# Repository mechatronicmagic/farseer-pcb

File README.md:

- [Repository Info](#org3efd3b6)
- [Images](#org4000d6c)
- [Schematic](#org9702aa9)
- [PCB](#orgc4c3abc)
- [Bill of Materials](#org9a89b54)
- [Development](#org04cc7a2)

    <!-- This file is generated automatically from metadata -->
    <!-- File edits may be overwritten! -->

# Repository Info

-   Project Name: farseer\_pcb
-   Synopsis: Measures fly wingbeats using IR light reflected from flapping fly wings.
-   Documentation Version: 1.0.0
-   Pcb Version: 1.0
-   Enclosure Version: 1.0
-   Supplemental BOM Version: 1.0
-   Release Date: 2025-05-16
-   Creation Date: 2025-05-16
-   Kicad Version: 9.0.0
-   License: GPL-3.0
-   URL: <https://github.com/mechatronicmagic/farseer_pcb>
-   Author: Peter Polidoro
-   Email: peter@polidoro.io
-   Copyright: 2025 Peter Polidoro
-   References:
    -   [kicad](https://www.kicad.org/)
    -   [light\_sensor\_boards](https://github.com/janelia-kicad/light_sensor_boards)
    -   [wingbeat\_detector](https://github.com/peterpolidoro/wingbeat_detector)
-   Papers:
    -   [Active antennal movements in Drosophila can tune wind encoding](https://doi.org/10.1016/j.cub.2023.01.020)
    -   [A novel assay to evaluate action selection in escape behavior](https://doi.org/10.1016/j.jneumeth.2018.04.019)
    -   [Cellular evidence for efference copy in Drosophila visuomotor processing](https://doi.org/10.1038/nn.4083)
    -   [State-dependent decoupling of sensory and motor circuits underlies behavioral flexibility in Drosophila](https://doi.org/10.1038/s41593-019-0413-4)
    -   [Active flight increases the gain of visual motion processing in Drosophila](https://doi.org/10.1038/nn.2492)
    -   [An Optical Tachometer for Measurement of the Wing-Beat Frequency of Free-Flying Insects](https://doi.org/10.1242/jeb.82.1.377)

This wingbeat detector, or flight “tachometer”, is a small electro-optical device that uses reflected infrared light from the fly’s wingbeats to generate an oscillating voltage signal. The oscillation frequency of the voltage signal matches, and thus allows one to measure, the tethered fly's wingbeat frequency.

This device is useful for plate (rather than pin) tethered flight experiments, because with plate-glued flies, one cannot extract the wingbeat frequency via a classical wingbeat analyzer. Microphones have also been used for extracting wingbeat frequency, but they require a quiet room. This wingbeat detector is immune to audible noise and only requires an infrared light source, often already present on flight rigs for video recording.

One end of a small diameter light guide is mounted near the fly and aimed at the wings. The other end of the light guide is in a small enclosure containing an optical filter and printed circuit board and can be mounted off to the side of the rig wherever there is room.

The light guide brings light reflected off of the wings down to a photodiode on a circuit board, after passing through an optical filter to remove the unwanted wavelengths of light. Amplifiers and filters on the circuit board convert the tiny amounts of current from the photodiode into an oscillating voltage signal, with a frequency range of several hundred Hertz and a magnitude range of several Volts.

The oscillating voltage signal can be fed into a data acquisition card, oscilloscope, and/or a speaker for recording and instant feedback on fly wingbeat frequency. Using a threshold, the signal can be used as a simple boolean that indicates whether the tethered animal is flying or not for triggering experiments or synchronizing the data collection.

This device was first created at Caltech in the Dickinson lab in collaboration with Gaby Maimon around 2010. It has transformed over several generations, getting smaller and more robust each iteration. It has been used on rigs in multiple universities and research institutes and has been referenced in several papers. A couple of iterations were designed in collaboration with Sung Soo Kim and the Card lab at Janelia Research Campus. The latest version was created in collaboration with the Suver lab at Vanderbilt.

# Images

# Schematic

[./documentation/schematic/wingbeat\_detector.pdf](./documentation/schematic/wingbeat_detector.pdf)

# PCB

# Bill of Materials

## Board

|    |
|--- |
|  |

## Supplemental

| Item | Description                        | Manufacturer Part Number | Manufacturer        | Quantity | Cost   | Total   |
|---- |---------------------------------- |------------------------ |------------------- |-------- |------ |------- |
| 1    | BNC STRAIGHT BULKHEAD JACK TO AM   | 095-850-210-150          | Amphenol RF         | 1        | 24.41  | 24.41   |
| 2    | AC/DC WALL MNT ADAPTER 5.1V 15W    | SC0445                   | Raspberry Pi        | 1        | 8.00   | 8.00    |
| 3    | CBL ASSY BNC PLUG-PLUG RG58 5'     | 5697-60                  | Pomona Electronics  | 1        | 21.29  | 21.29   |
| 4    | LLG 3 mm Core 420 - 2000 nm 1.2 m  | LLG3-4Z                  | thorlabs            | 1        | 392.69 | 392.69  |
| 5    | 3 mm LLG to SM1 Adapter            | AD3LLG                   | thorlabs            | 1        | 38.32  | 38.32   |
| 6    | Adapter External SM05 Internal SM1 | SM1A1                    | thorlabs            | 1        | 23.41  | 23.41   |
| 7    | SM05 Adjustable Lens Tube          | SM05V05                  | thorlabs            | 1        | 31.64  | 31.64   |
| 8    | 825nm 12.5mm Dia Longpass Filter   | 86-062                   | edmundoptics        | 1        | 194.00 | 194.00  |
| 9    | Universal probe holder             | MXB                      | siskiyou            | 1        | 275.00 | 275.00  |
| 10   | MACHINE SCREW PAN PHILLIPS 2-56    | PMSSS 256 0050 PH        | B&F Fastener Supply | 4        | 0.24   | 0.96    |
| 11   | HEX NUT 3/16" STN STEEL 2-56       | HNSS256                  | B&F Fastener Supply | 4        | 0.28   | 1.12    |
|      | Supplemental BOM Version: 1.0      |                          |                     |          | Total  | 1010.84 |

# Development

## Install Guix

[Install Guix](https://guix.gnu.org/manual/en/html_node/Binary-Installation.html)

## Edit metadata.org

    make metadata-edits

## Tangle metadata.org

    make metadata

## Edit project

    make kicad-edits
    exit

    make filter-edits
    exit

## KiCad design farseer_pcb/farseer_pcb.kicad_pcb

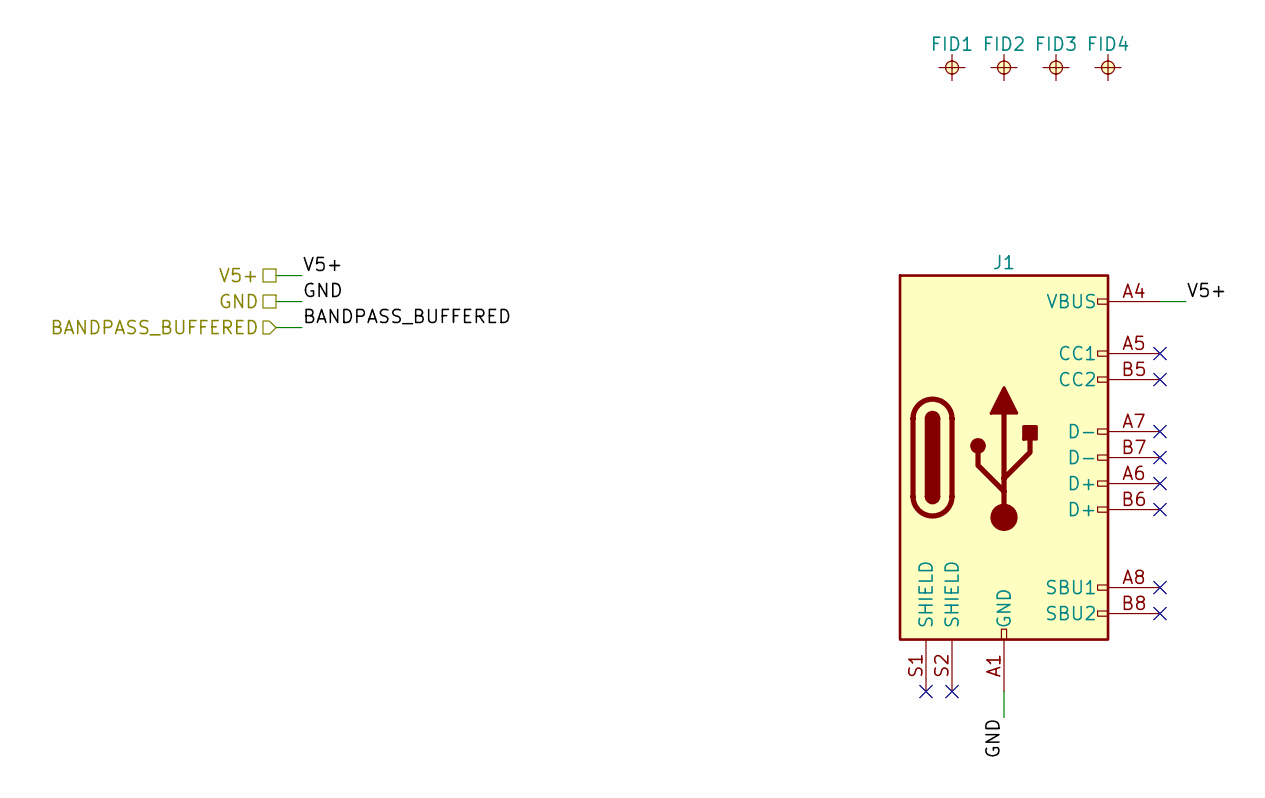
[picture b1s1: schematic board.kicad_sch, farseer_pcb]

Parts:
FID1, FID2, FID3, FID4: FIDUCIAL_0.5mm_MASK1mm; FIDUCIAL_0.5mm_Mask1mm
J1: Connector_USB_C_Receptacle_USB2.0_16P_GT-USB-7047C; USB_C_Receptacle_GT-USB-7047C_16P_TopMnt_Horizontal; Manufacturer Part Number GT-USB-7047C; LCSC C963218

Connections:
/GND: J1.A1 (GND), J1.A12 (GND), J1.B1 (GND), J1.B12 (GND); also elsewhere on the board
/V5+: J1.A4 (VBUS), J1.A9 (VBUS), J1.B4 (VBUS), J1.B9 (VBUS); also elsewhere on the board

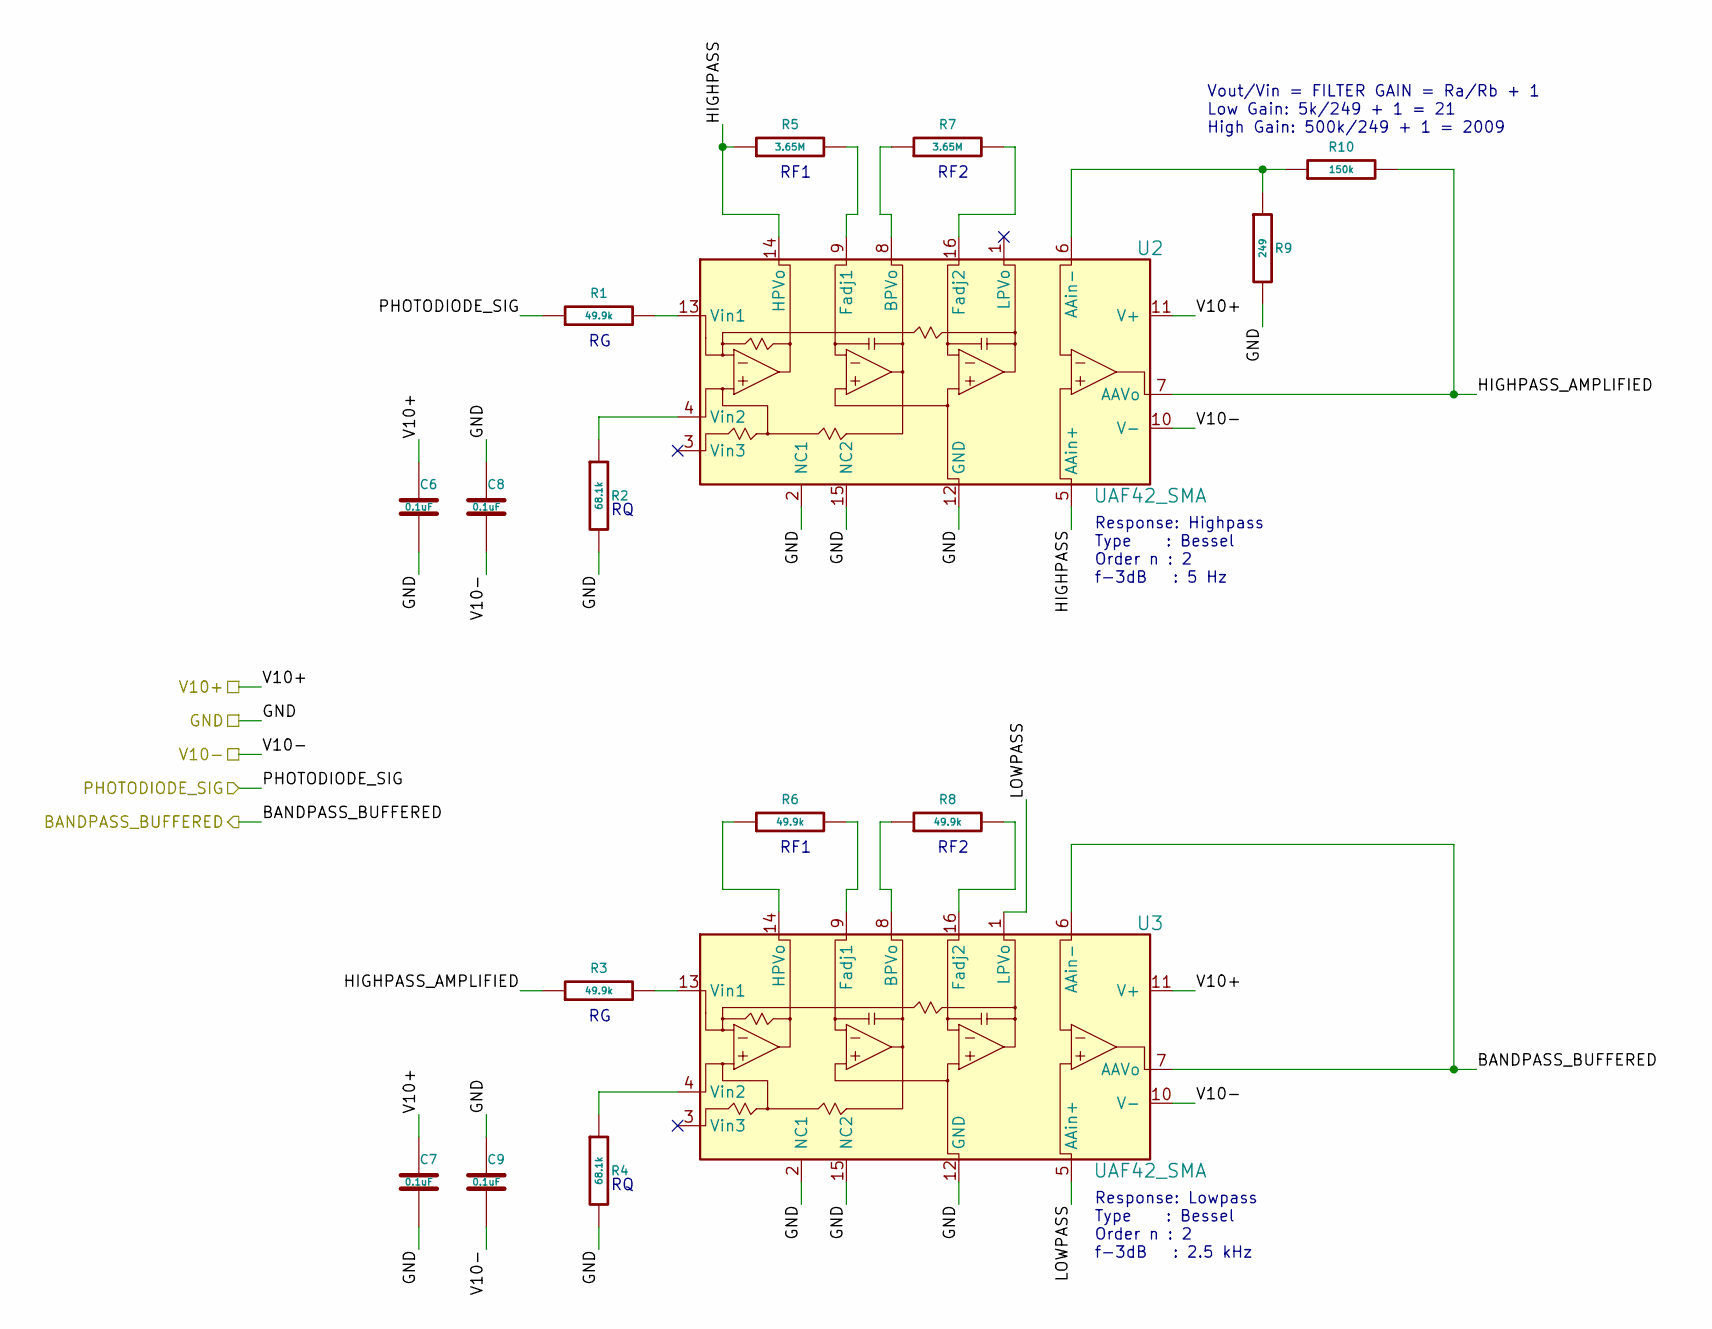
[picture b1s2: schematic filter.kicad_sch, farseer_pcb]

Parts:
C6, C7, C8, C9: 0.1uF; C_0402_1005Metric; Manufacturer Part Number CC0402ZRY5V8BB104
R1, R3, R6, R8: 49.9k; R_0402_1005Metric; Manufacturer Part Number ERJ-2RKF4992X
R2, R4: 68.1k; R_0402_1005Metric; Manufacturer Part Number ERJ-2RKF6812X
R5, R7: 3.65M; R_0603_1608Metric; Manufacturer Part Number CRCW06033M65FKEA
R9: 249; R_0402_1005Metric; Manufacturer Part Number ERJ-2RKF2490X
R10: 150k; R_1206_3216Metric; Manufacturer Part Number ERA-8AEB154V
U2, U3: UAF42_SMA; SOIC-16W_7.5x10.3mm_P1.27mm; Manufacturer Part Number UAF42AU

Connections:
/BANDPASS_BUFFERED: U3.6 (AAin-), U3.7 (AAVo)
/GND: C6.2, C7.2, C8.1, C9.1, R2.2, R4.2, R9.2, U2.2 (NC1), U2.12 (GND), U2.15 (NC2), U3.2 (NC1), U3.12 (GND), U3.15 (NC2); also elsewhere on the board
/PHOTODIODE_SIG: R1.1; also elsewhere on the board
/V10+: C6.1, C7.1, U2.11 (V+), U3.11 (V+); also elsewhere on the board
/V10-: C8.2, C9.2, U2.10 (V-), U3.10 (V-); also elsewhere on the board
/filter/HIGHPASS: R5.1, U2.5 (AAin+), U2.14 (HPVo)
/filter/HIGHPASS_AMPLIFIED: R3.1, R10.2, U2.7 (AAVo)
/filter/LOWPASS: U3.1 (LPVo), U3.5 (AAin+)
unnamed: R9.1, R10.1, U2.6 (AAin-)
unnamed: R7.1, U2.8 (BPVo)
unnamed: R5.2, U2.9 (Fadj1)
unnamed: R7.2, U2.16 (Fadj2)
unnamed: R1.2, U2.13 (Vin1)
unnamed: R2.1, U2.4 (Vin2)
unnamed: R8.1, U3.8 (BPVo)
unnamed: R6.2, U3.9 (Fadj1)
unnamed: R8.2, U3.16 (Fadj2)
unnamed: R6.1, U3.14 (HPVo)
unnamed: R3.2, U3.13 (Vin1)
unnamed: R4.1, U3.4 (Vin2)

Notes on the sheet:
RF2
Response: Lowpass Type : Bessel Order n : 2 f-3dB : 2.5 kHz
RF1
Vout/Vin = FILTER GAIN = Ra/Rb + 1 Low Gain: 5k/249 + 1 = 21 High Gain: 500k/249 + 1 = 2009
Response: Highpass Type : Bessel Order n : 2 f-3dB : 5 Hz

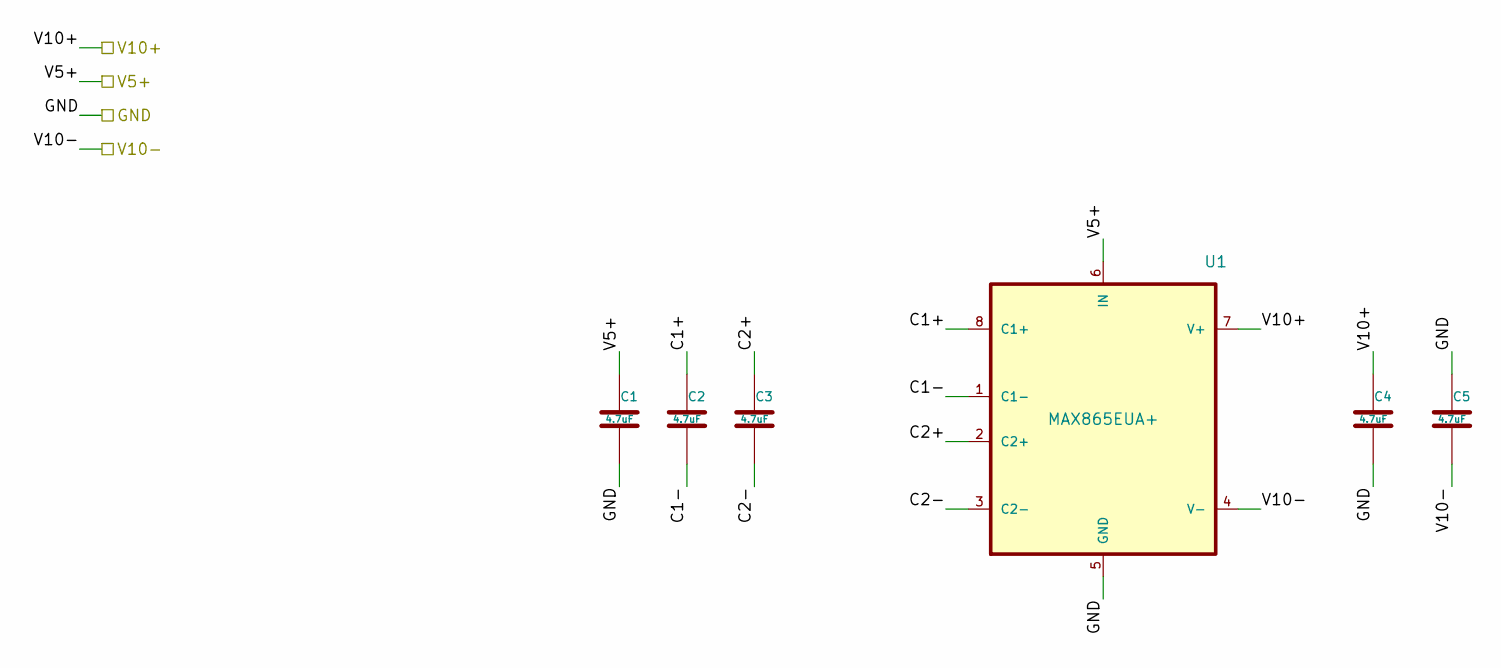
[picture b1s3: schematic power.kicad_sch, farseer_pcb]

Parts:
C1, C2, C3, C4, C5: 4.7uF; C_0603_1608Metric; Manufacturer Part Number C1608X5R1C475K080AC
U1: MAX865EUA+; SOP65P490X110-8N; Manufacturer Part Number MAX865EUA+

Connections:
/GND: C1.2, C4.2, C5.1, U1.5 (GND); also elsewhere on the board
/V5+: C1.1, U1.6 (IN); also elsewhere on the board
/V10+: C4.1, U1.7 (V+); also elsewhere on the board
/V10-: C5.2, U1.4 (V-); also elsewhere on the board
/power/C1+: C2.1, U1.8 (C1+)
/power/C1-: C2.2, U1.1 (C1-)
/power/C2+: C3.1, U1.2 (C2+)
/power/C2-: C3.2, U1.3 (C2-)

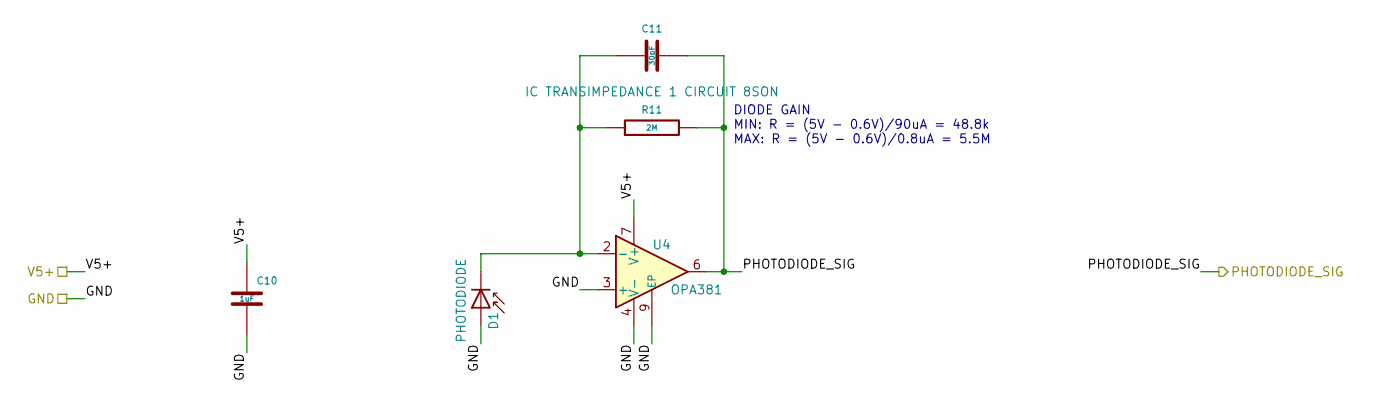
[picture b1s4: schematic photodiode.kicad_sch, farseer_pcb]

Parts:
C10: 1uF; C_0402_1005Metric; Manufacturer Part Number CL05A105KL5NRNC; LCSC C307413
C11: 30pF; C_0402_1005Metric; Manufacturer Part Number C0402C300J5GACAUTO
D1: PHOTODIODE; PHOTODIODE_RADIAL_RA_SMD_BRIGHT; Manufacturer Part Number BPD-BQDA38V-FZ04
R11: 2M; R_1206_3216Metric; Manufacturer Part Number ERJ-PM8F2004V
U4: OPA381; VSON-8-1EP_3x3mm_P0.65mm_EP1.65x2.4mm; Manufacturer Part Number OPA381AIDRBT

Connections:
/GND: C10.2, D1.2 (A), U4.3 (+), U4.4 (V-), U4.9 (EP); also elsewhere on the board
/PHOTODIODE_SIG: C11.2, R11.2, U4.6; also elsewhere on the board
/V5+: C10.1, U4.7 (V+); also elsewhere on the board
unnamed: C11.1, D1.1 (K), R11.1, U4.2 (-)

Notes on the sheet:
DIODE GAIN MIN: R = (5V - 0.6V)/90uA = 48.8k MAX: R = (5V - 0.6V)/0.8uA = 5.5M

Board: 4 copper layers, 32 parts (19 on the bottom side), 26 nets, no tracks yet.

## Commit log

2025-05-16 Do not remove components from simulation
2025-05-16 Update config data
2025-05-16 Update filter design
2025-05-20 Begin board resize
2025-05-20 Add filter to supplemental bom
